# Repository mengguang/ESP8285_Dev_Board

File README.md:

# ESP8285_Dev_Board
ESP8285 Development Board with PCB Antenna.

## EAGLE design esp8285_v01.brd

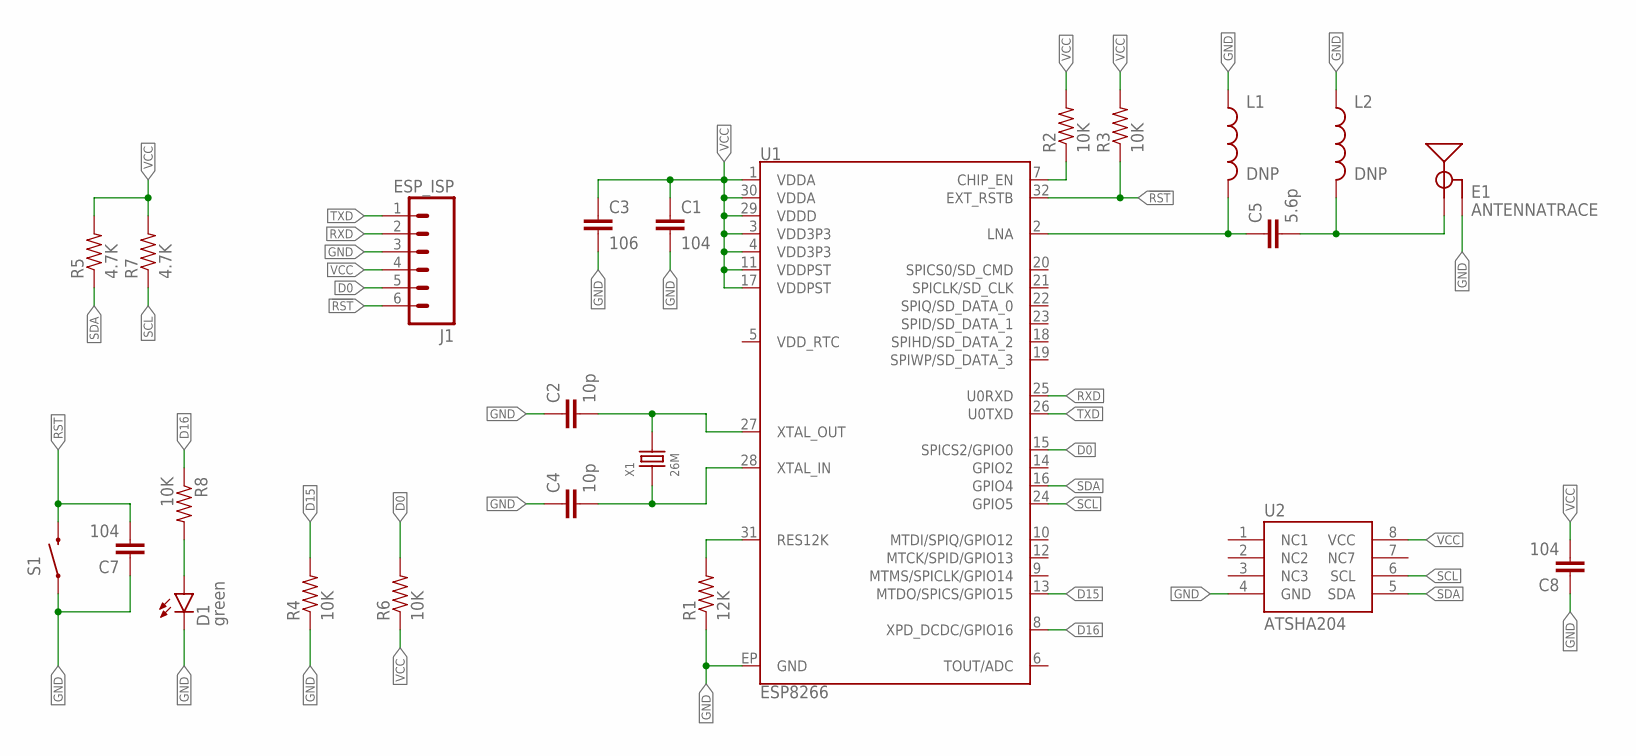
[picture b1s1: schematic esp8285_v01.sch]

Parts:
C1, C7, C8: 104; 0402-CAP
C2, C4: 10p; 0402-CAP
C3: 106; 0402-CAP
C5: 5.6p; 0402-CAP
D1: green; LED-0603-EASY
E1: ANTENNATRACE; TRACE_ANTENNA_2.4GHZ_25.7MM
J1: ESP_ISP; 1X06_NO_SILK
L1, L2: DNP; C0402
R1: 12K; 0402-RES
R2, R3, R4, R6, R8: 10K; 0402-RES
R5, R7: 4.7K; 0402-RES
S1: SWITCH-MOMENTARY-2SMD-1101NE; TACTILE-SWITCH-1101NE
U1: ESP8266; QFN32
U2: ATSHA204; SO08
X1: 26M; X4-SMD-3.2X2.5X0.7MM

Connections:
!RST: C7.2, J1.6, R3.1, S1.2, U1.32 (EXT_RSTB)
D0: J1.5, R6.2, U1.15 (SPICS2/GPIO0)
D15: R4.2, U1.13 (MTDO/SPICS/GPIO15)
D16: R8.1, U1.8 (XPD_DCDC/GPIO16)
GND: C1.2, C2.1, C3.2, C4.1, C7.1, C8.1, D1.- (C), E1.GND, E1.GND2 (GND), J1.3, L1.1, L2.1, R1.1, R4.1, S1.1, U1.EP (GND), U2.4 (GND)
unnamed: C2.2, U1.27 (XTAL_OUT), X1.3 (2)
unnamed: C4.2, U1.28 (XTAL_IN), X1.1
unnamed: R1.2, U1.31 (RES12K)
unnamed: C5.1, L1.2, U1.2 (LNA)
unnamed: C5.2, E1.ANT (SIGNAL), L2.2
unnamed: R2.1, U1.7 (CHIP_EN)
unnamed: D1.+ (A), R8.2
RXD: J1.2, U1.25 (U0RXD)
SCL: R7.1, U1.24 (GPIO5), U2.6 (SCL)
SDA: R5.1, U1.16 (GPIO4), U2.5 (SDA)
TXD: J1.1, U1.26 (U0TXD)
VCC: C1.1, C3.1, C8.2, J1.4, R2.2, R3.2, R5.2, R6.1, R7.2, U1.1 (VDDA), U1.3 (VDD3P3), U1.4 (VDD3P3), U1.11 (VDDPST), U1.17 (VDDPST), U1.29 (VDDD), U1.30 (VDDA), U2.8 (VCC)

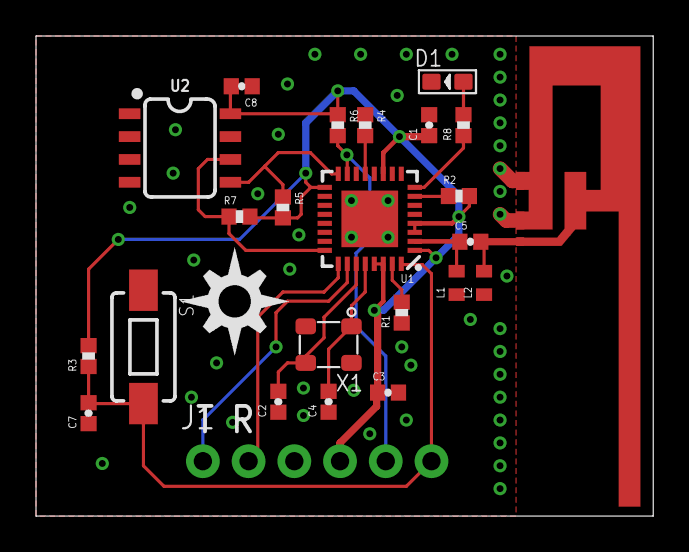
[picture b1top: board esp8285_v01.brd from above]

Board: 2 copper layers, 34.3 x 26.7 mm, 25 parts (0 on the bottom side), 17 nets.

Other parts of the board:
U$1: DIYNOVA_LOGO

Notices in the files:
parts and their libraries:
SparkFun-RF: Licensing: Creative Commons ShareAlike 4.0 International - https://creativecommons.org/licenses/by-sa/4.0
